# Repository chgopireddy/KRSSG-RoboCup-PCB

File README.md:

# KRSSG-RoboCup-PCB
Eagle PCB Design Files of RoboCup Hardware

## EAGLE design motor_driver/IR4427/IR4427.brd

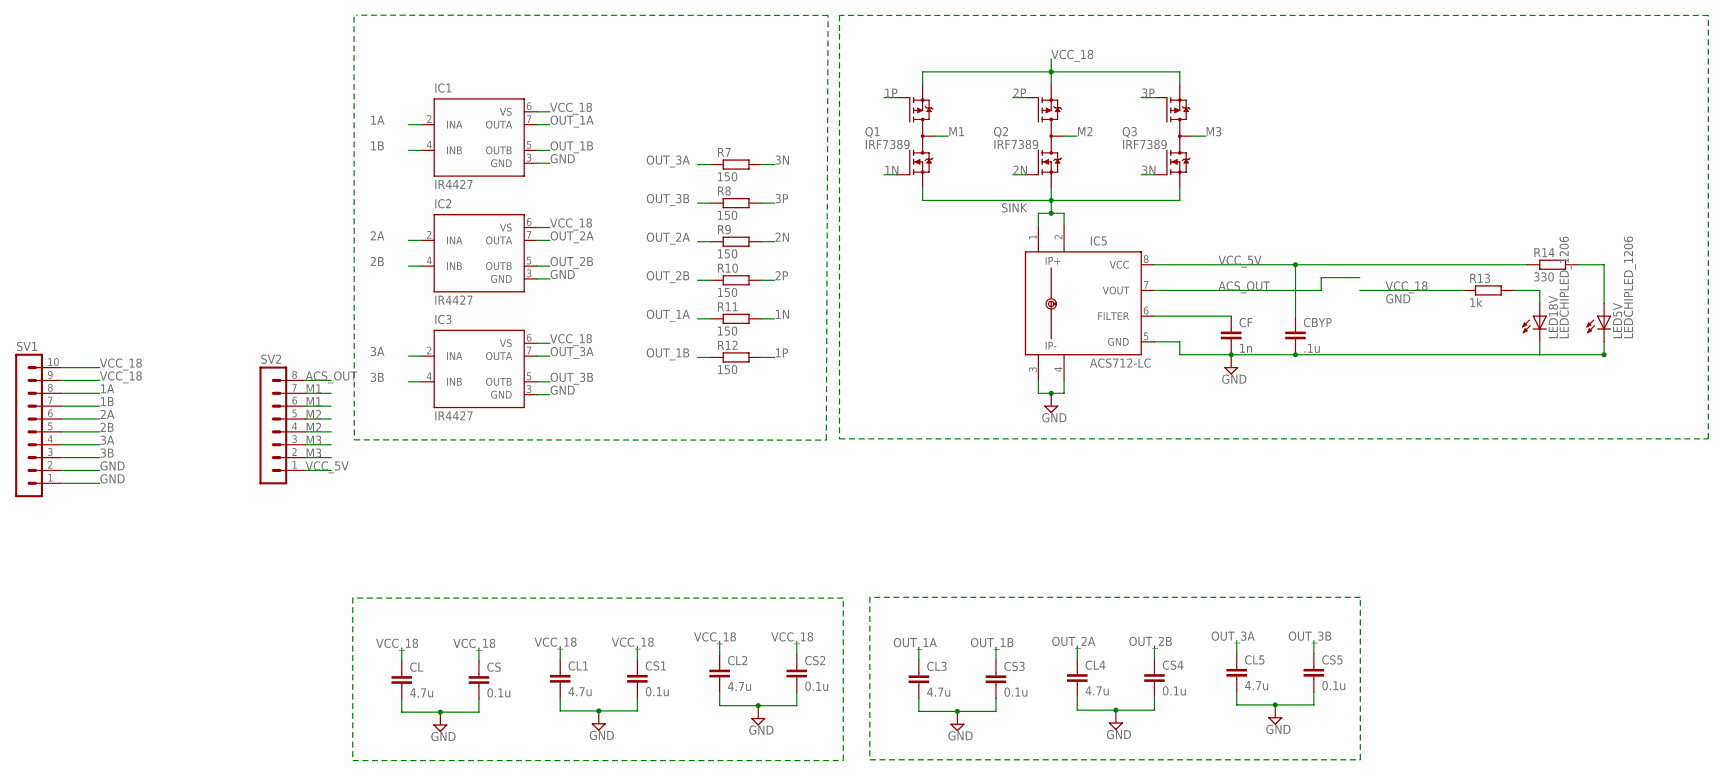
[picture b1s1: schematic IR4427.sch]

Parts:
CBYP: .1u; C1206
CF: 1n; C1206
CL, CL1, CL2, CL3, CL4, CL5: 4.7u; C1206
CS, CS1, CS2, CS3, CS4, CS5: 0.1u; C1206
IC1, IC2, IC3: IR4427; DIL08
IC5: ACS712-LC; SOIC8
LED5V, LED18V: LEDCHIPLED_1206; CHIPLED_1206
Q1, Q2, Q3: IRF7389; SO08-IRF
R7, R8, R9, R10, R11, R12: 150; R1206
R13: 1k; R1206
R14: 330; R1206
SV1: MA10-1
SV2: MA08-1

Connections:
1A: IC1.2 (INA), SV1.8
1B: IC1.4 (INB), SV1.7
1N: Q1.2 (N-G), R11.2
1P: Q1.4 (P-G), R12.2
2A: IC2.2 (INA), SV1.6
2B: IC2.4 (INB), SV1.5
2N: Q2.2 (N-G), R9.2
2P: Q2.4 (P-G), R10.2
3A: IC3.2 (INA), SV1.4
3B: IC3.4 (INB), SV1.3
3N: Q3.2 (N-G), R7.2
3P: Q3.4 (P-G), R8.2
ACS_OUT: IC5.7 (VOUT), SV2.8
GND: CBYP.2, CF.2, CL.2, CL1.2, CL2.2, CL3.2, CL4.2, CL5.2, CS.2, CS1.2, CS2.2, CS3.2, CS4.2, CS5.2, IC1.3 (GND), IC2.3 (GND), IC3.3 (GND), IC5.3 (IP-), IC5.4 (IP-1), IC5.5 (GND), LED5V.C, LED18V.C, SV1.1, SV1.2
M1: Q1.5 (D), Q1.6 (D), Q1.7 (D), Q1.8 (D), SV2.6, SV2.7
M2: Q2.5 (D), Q2.6 (D), Q2.7 (D), Q2.8 (D), SV2.4, SV2.5
M3: Q3.5 (D), Q3.6 (D), Q3.7 (D), Q3.8 (D), SV2.2, SV2.3
unnamed: LED18V.A, R13.2
unnamed: CF.1, IC5.6 (FILTER)
unnamed: LED5V.A, R14.2
OUT_1A: CL3.1, IC1.7 (OUTA), R11.1
OUT_1B: CS3.1, IC1.5 (OUTB), R12.1
OUT_2A: CL4.1, IC2.7 (OUTA), R9.1
OUT_2B: CS4.1, IC2.5 (OUTB), R10.1
OUT_3A: CL5.1, IC3.7 (OUTA), R7.1
OUT_3B: CS5.1, IC3.5 (OUTB), R8.1
SINK: IC5.1 (IP+), IC5.2 (IP+1), Q1.1 (N-S), Q2.1 (N-S), Q3.1 (N-S)
VCC_5V: CBYP.1, IC5.8 (VCC), R14.1, SV2.1
VCC_18: CL.1, CL1.1, CL2.1, CS.1, CS1.1, CS2.1, IC1.6 (VS), IC2.6 (VS), IC3.6 (VS), Q1.3 (P-S), Q2.3 (P-S), Q3.3 (P-S), R13.1, SV1.9, SV1.10

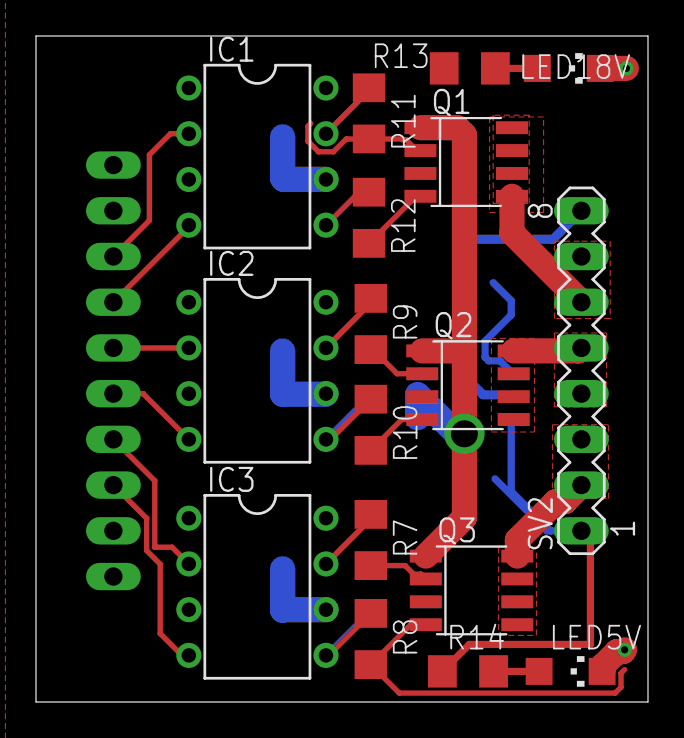
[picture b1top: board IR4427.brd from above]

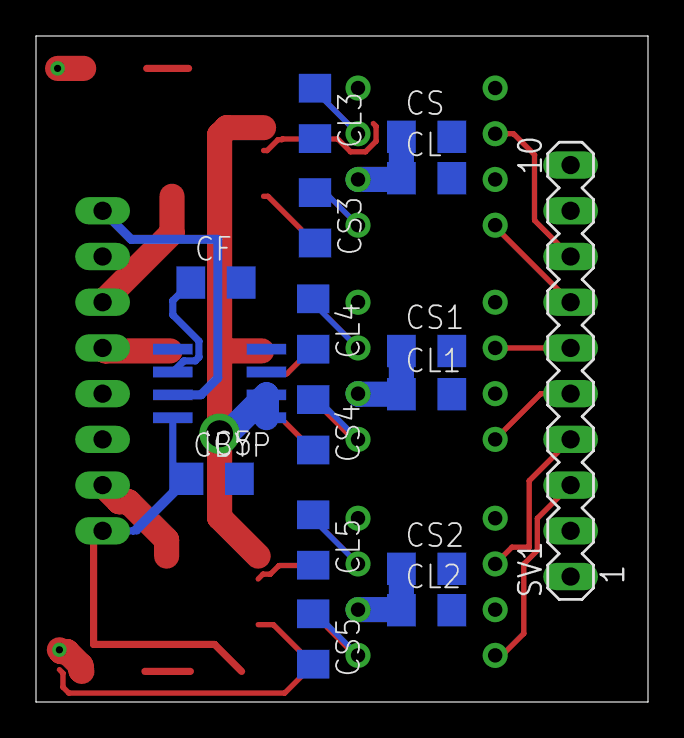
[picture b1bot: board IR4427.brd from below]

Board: 2 copper layers, 34.0 x 37.0 mm, 33 parts (16 on the bottom side), 29 nets.

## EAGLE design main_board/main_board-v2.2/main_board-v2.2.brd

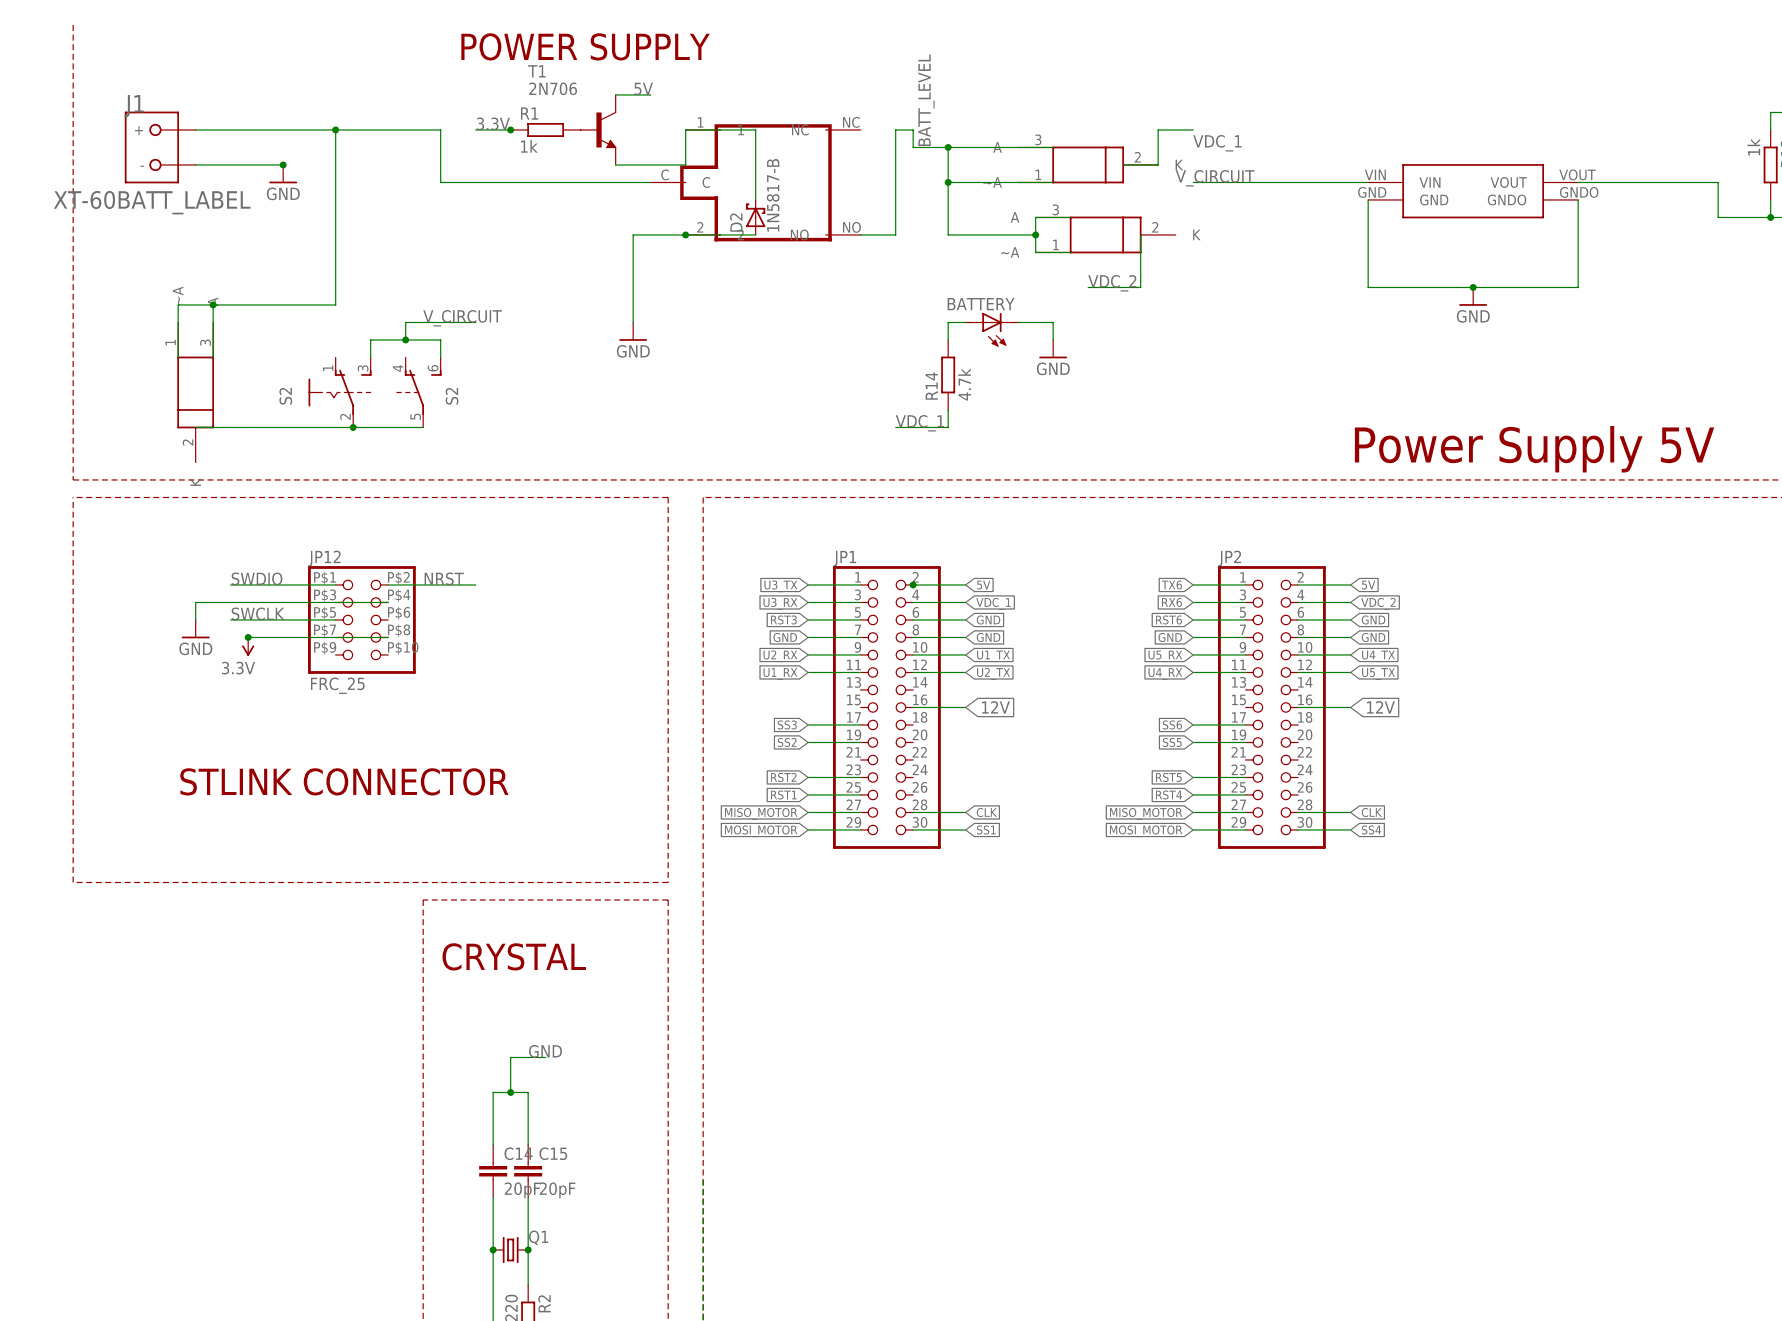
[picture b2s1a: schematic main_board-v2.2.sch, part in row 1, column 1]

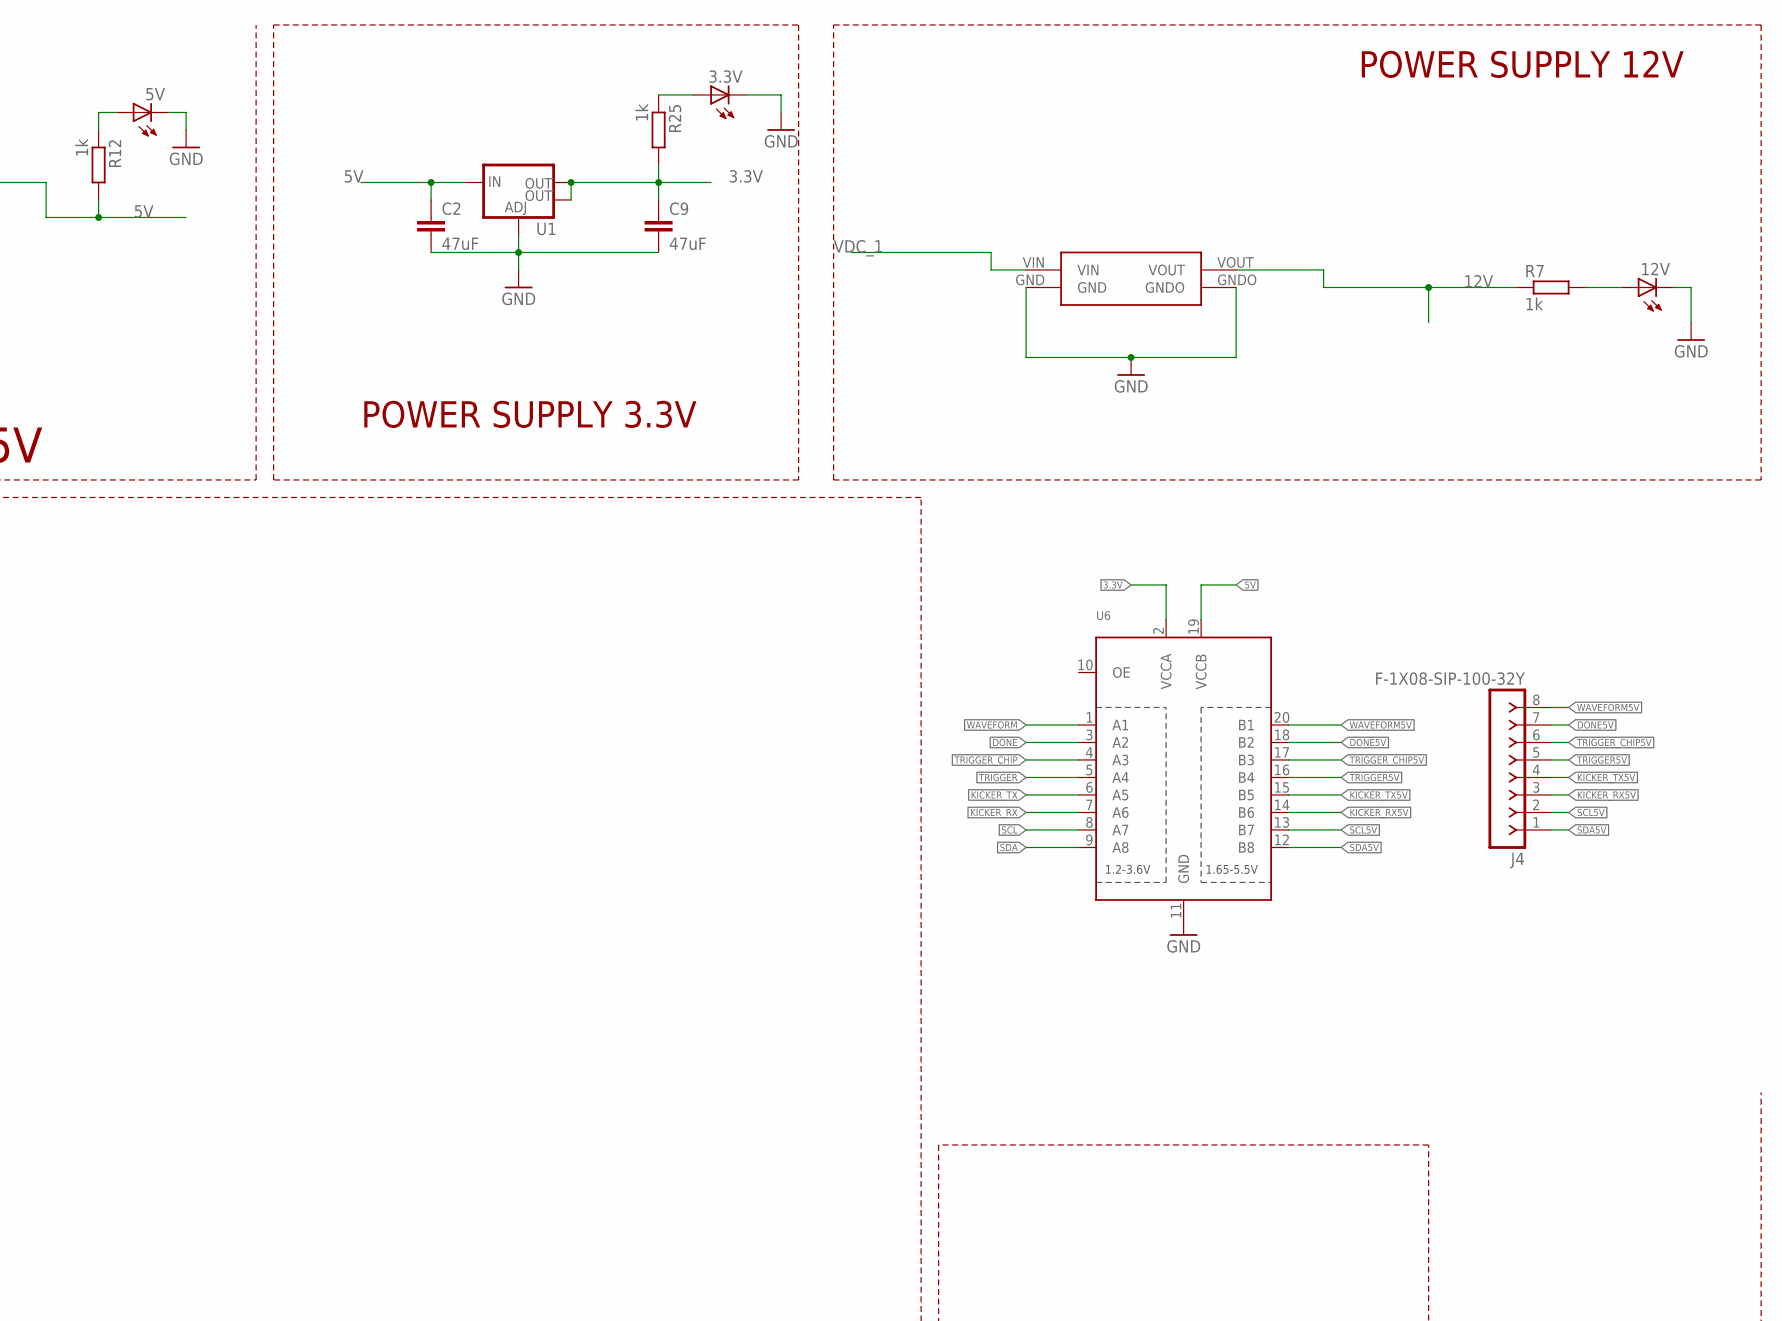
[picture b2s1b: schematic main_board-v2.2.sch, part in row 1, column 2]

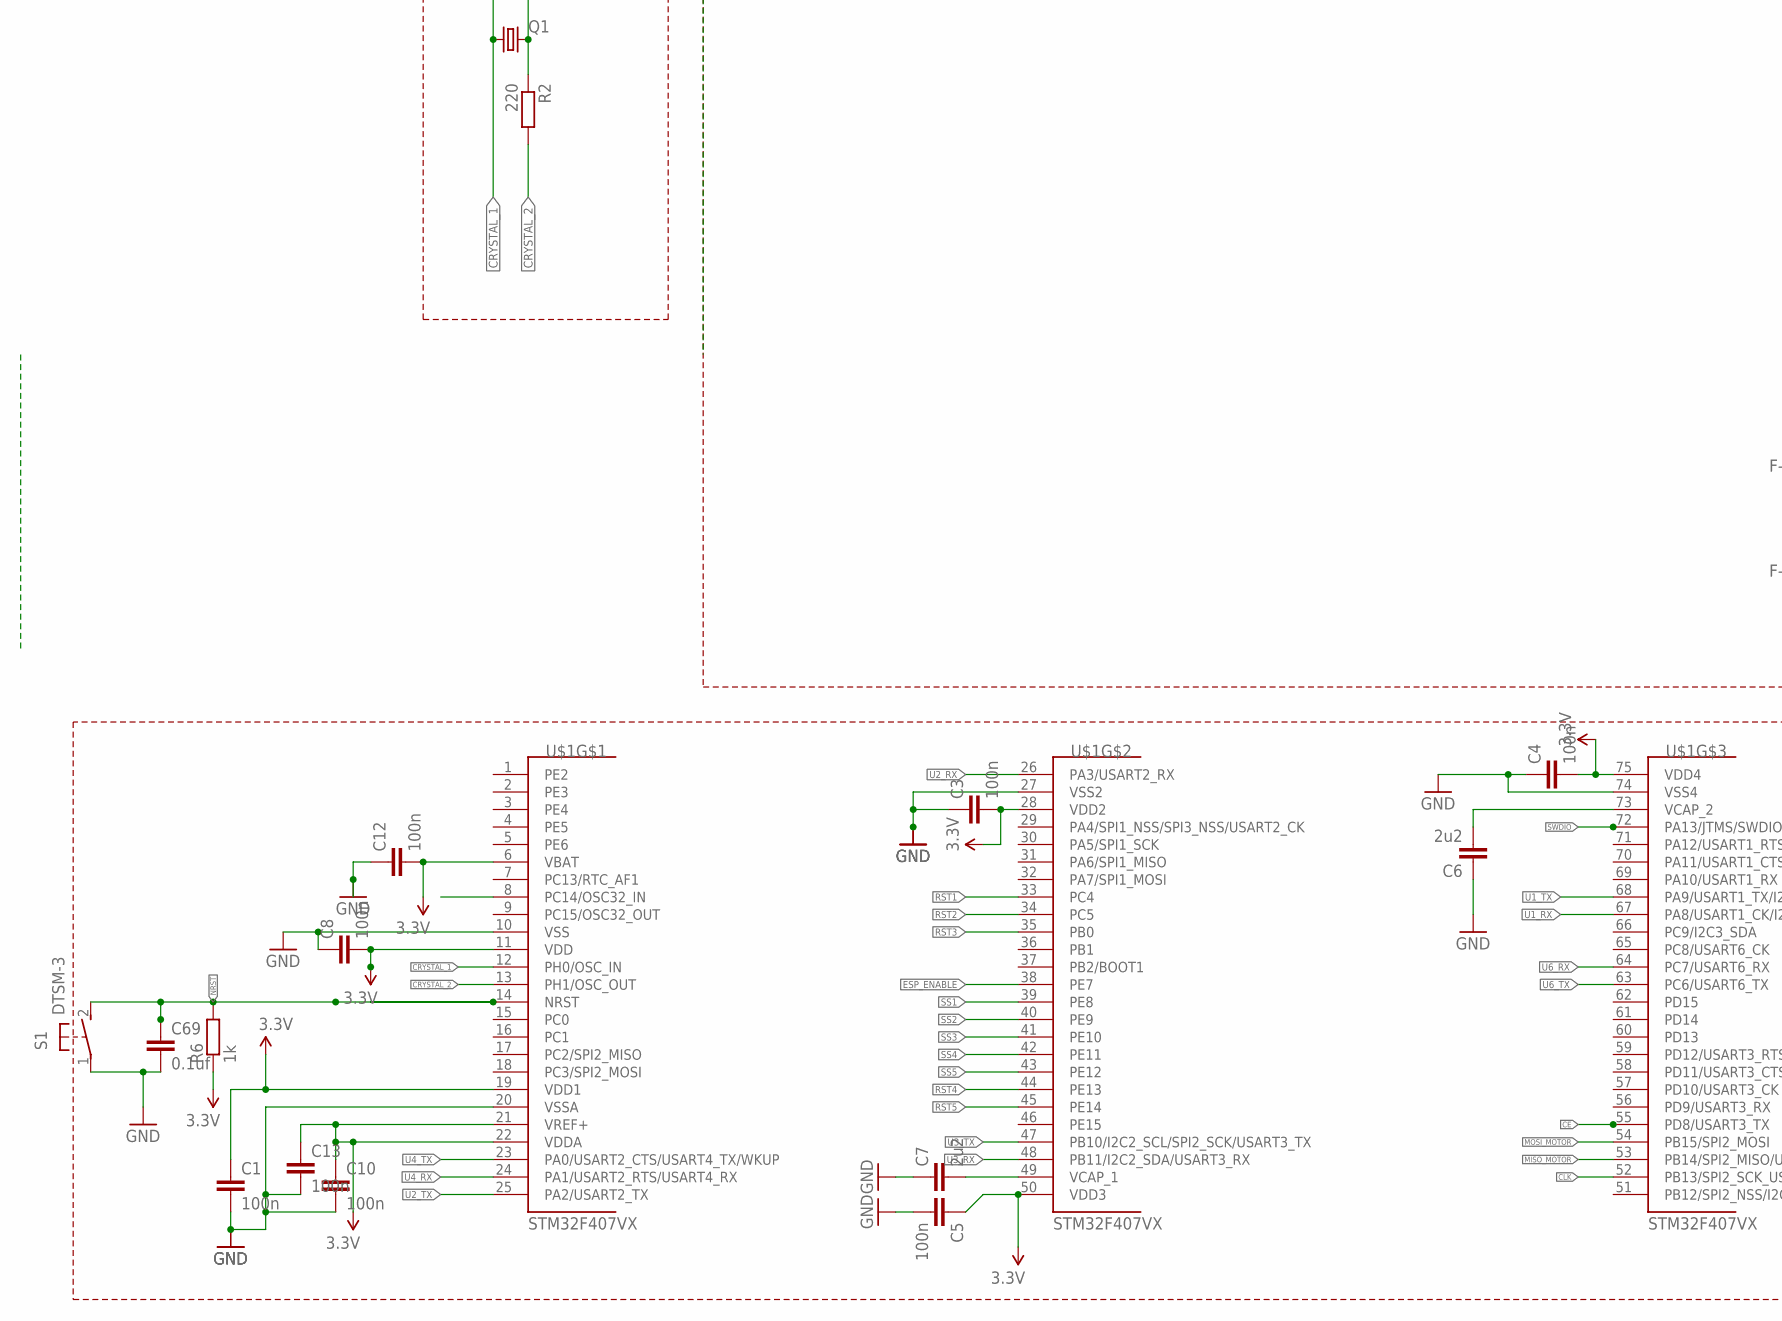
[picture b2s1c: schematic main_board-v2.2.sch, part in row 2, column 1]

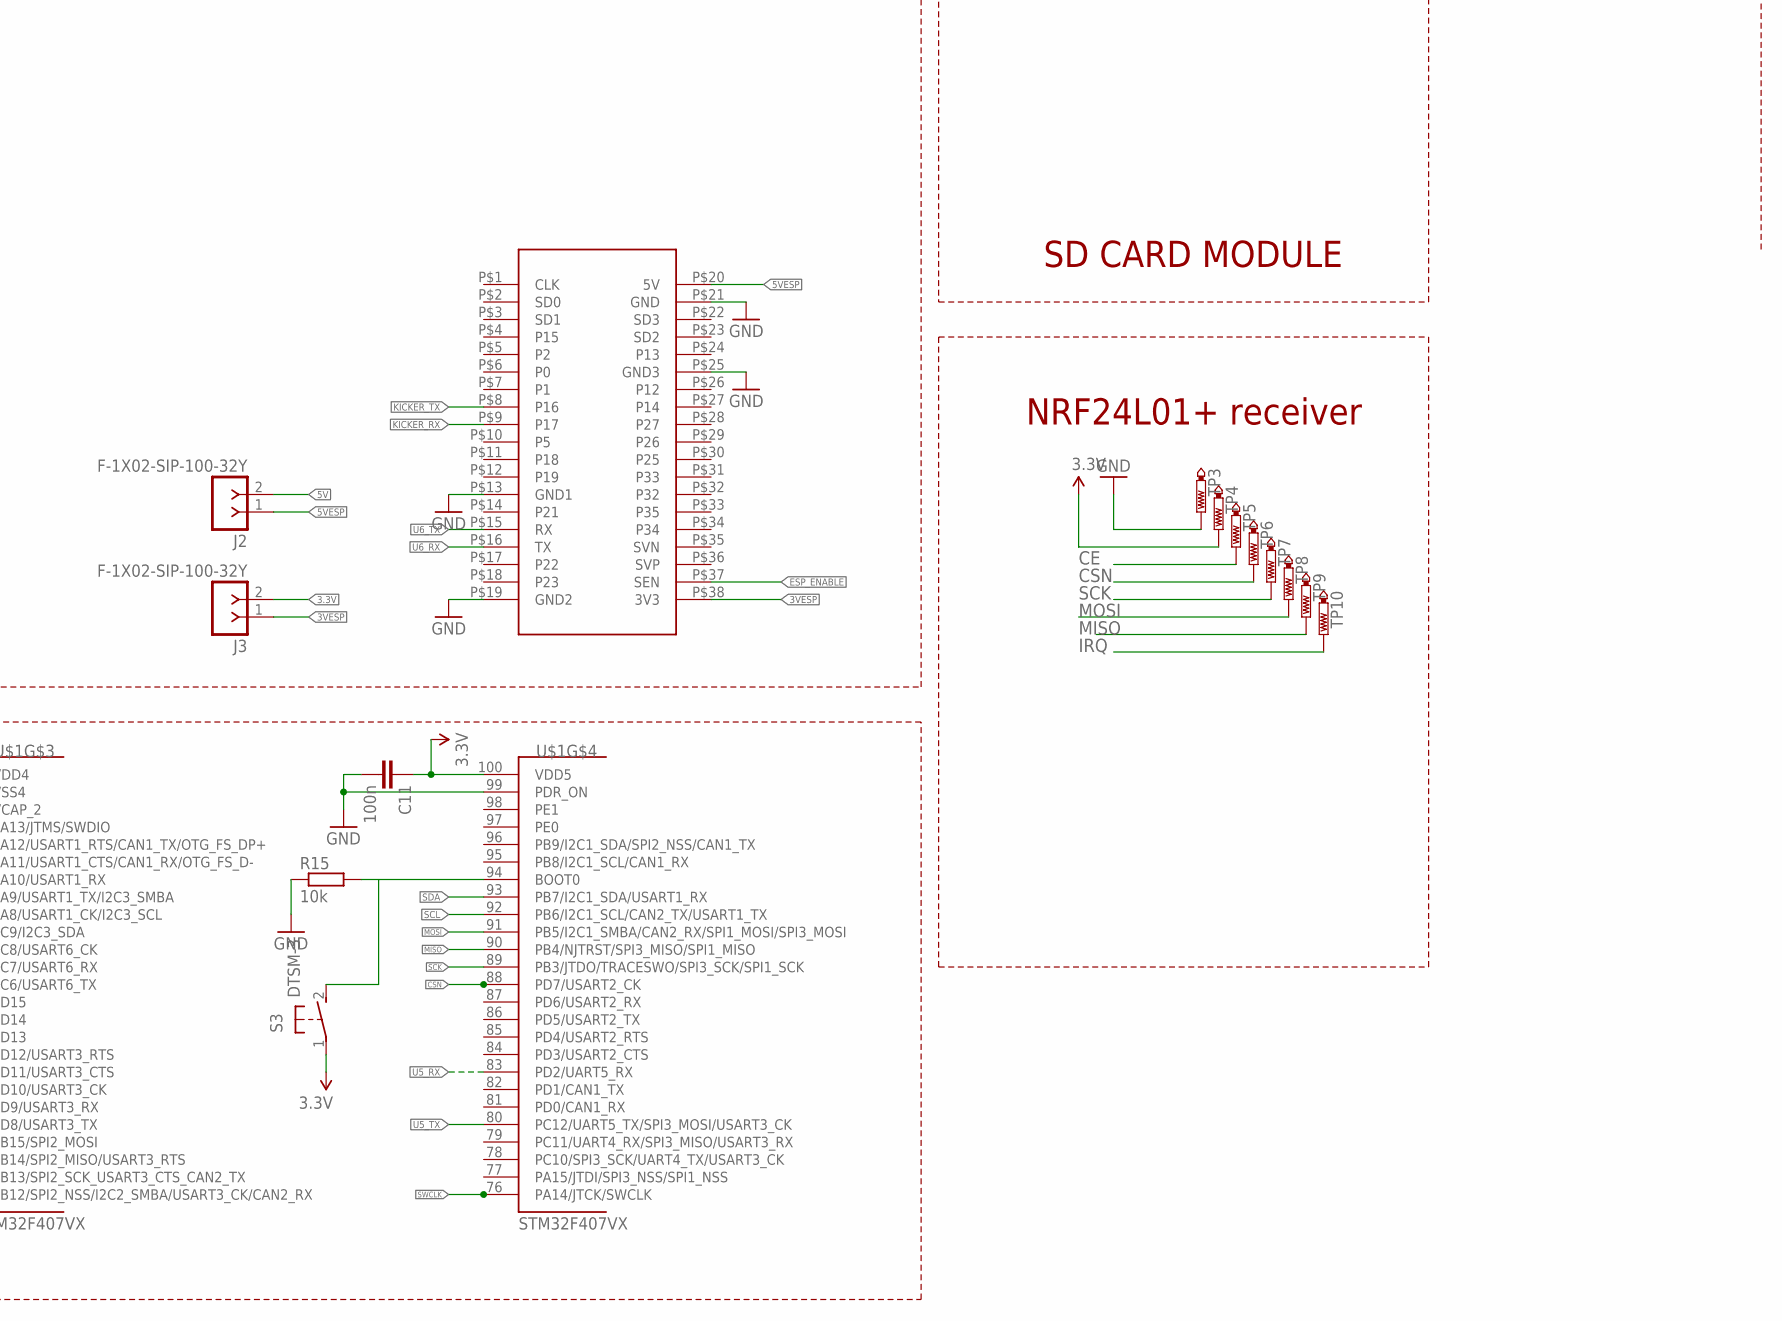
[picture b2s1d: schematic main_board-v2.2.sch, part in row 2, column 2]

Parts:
3.3V, 5V, 12V: LEDCHIPLED_0805; CHIPLED_0805
BATTERY: LEDCHIPLED_0805; CHIPLED_0805
C1, C3, C4, C5, C8, C10, C11, C12, C13: 100n; C1206
C2, C9: 47uF; C1206
C6, C7: 2u2; C1206
C14, C15: 20pF; C1206
C69: 0.1uf; C1206
D2: 1N5817-B; DO41-7.6
J1: XT-60BATT_LABEL; XT-60
J2, J3: F-1X02-SIP-100-32Y; SIP-100-02-32Y
J4: F-1X08-SIP-100-32Y; SIP-100-08-32Y
JP1, JP2: PINHD-2X15_2.54; 2X15
JP12: FRC_25; FRC2*5
Q1: CRYSTALHC49U-V; HC49U-V
R1, R6, R7, R12, R25: 1k; R1206
R2: 220; R1206
R14: 4.7k; R1206
R15: 10k; R1206
S1, S3: DTSM-3
S2: A68-A31
T1: 2N706; TO18
TP3, TP4, TP5, TP6, TP7, TP8, TP9, TP10: PTR1PAD1-13; P1-13
U1: V_REG_LM1117SOT223; SOT223
U2, U3, U4: LP38690DT-3.3; TO228P1042X238-3N
U6: TXB0108PWR; TSSOP20
U$1: STM32F407VX; LQFP100
U$2: REL
U$3, U$4: BUCK
U$6: NODEMCU32S; NODEMCU32

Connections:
3.3V: C1.1, C3.2, C4.2, C5.1, C8.2, C9.1, C10.1, C11.1, C12.2, C13.1, J3.2, JP12.P$7 (7), JP12.P$8 (8), R1.1, R6.1, R25.2, S3.1, TP4.TP, U1.2 (OUT), U1.4 (OUT), U6.2 (VCCA), U$1.6 (VBAT), U$1.11 (VDD), U$1.19 (VDD1), U$1.21 (VREF+), U$1.22 (VDDA), U$1.28 (VDD2), U$1.50 (VDD3), U$1.75 (VDD4), U$1.100 (VDD5)
3VESP: J3.1, U$6.P$38 (3V3)
5V: C2.1, J2.2, JP1.2, JP2.2, R12.2, T1.3 (C), U1.3 (IN), U6.19 (VCCB), U$3.VOUT
5VESP: J2.1, U$6.P$20 (5V)
12V: JP1.16, JP2.16, R7.1, U$4.VOUT
BATT_LEVEL: U2.1 (~A), U2.3 (A), U4.1 (~A), U4.3 (A), U$2.NO
CE: TP5.TP, U$1.55 (PD8/USART3_TX)
CLK: JP1.28, JP2.28, U$1.52 (PB13/SPI2_SCK_USART3_CTS_CAN2_TX)
CRYSTAL_1: C14.2, Q1.1, U$1.12 (PH0/OSC_IN)
CRYSTAL_2: R2.2, U$1.13 (PH1/OSC_OUT)
CSN: TP6.TP, U$1.88 (PD7/USART2_CK)
DONE: U6.3 (A2)
DONE5V: J4.7, U6.18 (B2)
ESP_ENABLE: U$1.38 (PE7), U$6.P$37 (SEN)
GND: 3.3V.C, 5V.C, 12V.C, BATTERY.C, C1.2, C2.2, C3.1, C4.1, C5.2, C6.1, C7.1, C8.1, C9.2, C10.2, C11.2, C12.1, C13.2, C14.1, C15.1, C69.2, D2.A, J1.GND (-), JP1.6, JP1.7, JP1.8, JP2.6, JP2.7, JP2.8, JP12.P$3 (3), JP12.P$4 (4), R15.1, S1.1, TP3.TP, U1.1 (ADJ), U6.11 (GND), U$1.10 (VSS), U$1.20 (VSSA), U$1.27 (VSS2), U$1.74 (VSS4), U$1.99 (PDR_ON), U$2.2, U$3.GND, U$3.GNDO, U$4.GND, U$4.GNDO, U$6.P$13 (GND1), U$6.P$19 (GND2), U$6.P$21 (GND), U$6.P$25 (GND3)
INPUT: J1.BATT (+), U3.1 (~A), U3.3 (A), U$2.C
IRQ: TP10.TP
IRQ_SPI2: U$1.8 (PC14/OSC32_IN)
KICKER_RX: U6.7 (A6), U$6.P$9 (P17)
KICKER_RX5V: J4.3, U6.14 (B6)
KICKER_TX: U6.6 (A5), U$6.P$8 (P16)
KICKER_TX5V: J4.4, U6.15 (B5)
MISO: TP9.TP, U$1.90 (PB4/NJTRST/SPI3_MISO/SPI1_MISO)
MISO_MOTOR: JP1.27, JP2.27, U$1.53 (PB14/SPI2_MISO/USART3_RTS)
MOSI: TP8.TP, U$1.91 (PB5/I2C1_SMBA/CAN2_RX/SPI1_MOSI/SPI3_MO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)
MOSI_MOTOR: JP1.29, JP2.29, U$1.54 (PB15/SPI2_MOSI)
unnamed: C7.2, U$1.49 (VCAP_1)
unnamed: C6.2, U$1.73 (VCAP_2)
unnamed: R15.2, S3.2, U$1.94 (BOOT0)
unnamed: C15.2, Q1.2, R2.1
unnamed: 5V.A, R12.1
unnamed: 12V.A, R7.2
unnamed: BATTERY.A, R14.2
unnamed: 3.3V.A, R25.1
unnamed: R1.2, T1.2 (B)
unnamed: D2.C, T1.1 (E), U$2.1
unnamed: S2.2, S2.5, U3.2 (K)
NRST: C69.1, JP12.P$2 (2), R6.2, S1.2, U$1.14 (NRST)
RST1: JP1.25, U$1.33 (PC4)
RST2: JP1.23, U$1.34 (PC5)
RST3: JP1.5, U$1.35 (PB0)
RST4: JP2.25, U$1.44 (PE13)
RST5: JP2.23, U$1.45 (PE14)
RST6: JP2.5
RX6: JP2.3
SCK: TP7.TP, U$1.89 (PB3/JTDO/TRACESWO/SPI3_SCK/SPI1_SCK)
SCL: U6.8 (A7), U$1.92 (PB6/I2C1_SCL/CAN2_TX/USART1_TX)
SCL5V: J4.2, U6.13 (B7)
SDA: U6.9 (A8), U$1.93 (PB7/I2C1_SDA/USART1_RX)
SDA5V: J4.1, U6.12 (B8)
SS1: JP1.30, U$1.39 (PE8)
SS2: JP1.19, U$1.40 (PE9)
SS3: JP1.17, U$1.41 (PE10)
SS4: JP2.30, U$1.42 (PE11)
SS5: JP2.19, U$1.43 (PE12)
SS6: JP2.17
SWCLK: JP12.P$5 (5), U$1.76 (PA14/JTCK/SWCLK)
SWDIO: JP12.P$1 (1), U$1.72 (PA13/JTMS/SWDIO)
TRIGGER: U6.5 (A4)
TRIGGER5V: J4.5, U6.16 (B4)
TRIGGER_CHIP: U6.4 (A3)
TRIGGER_CHIP5V: J4.6, U6.17 (B3)
TX6: JP2.1
U1_RX: JP1.11, U$1.67 (PA8/USART1_CK/I2C3_SCL)
U1_TX: JP1.10, U$1.68 (PA9/USART1_TX/I2C3_SMBA)
U2_RX: JP1.9, U$1.26 (PA3/USART2_RX)
U2_TX: JP1.12, U$1.25 (PA2/USART2_TX)
U3_RX: JP1.3, U$1.48 (PB11/I2C2_SDA/USART3_RX)
U3_TX: JP1.1, U$1.47 (PB10/I2C2_SCL/SPI2_SCK/USART3_TX)
U4_RX: JP2.11, U$1.24 (PA1/USART2_RTS/USART4_RX)
U4_TX: JP2.10, U$1.23 (PA0/USART2_CTS/USART4_TX/WKUP)
U5_RX: JP2.9, U$1.83 (PD2/UART5_RX)
U5_TX: JP2.12, U$1.80 (PC12/UART5_TX/SPI3_MOSI/USART3_CK)
U6_RX: U$1.64 (PC7/USART6_RX), U$6.P$16 (TX)
U6_TX: U$1.63 (PC6/USART6_TX), U$6.P$15 (RX)
VDC_1: JP1.4, R14.1, U4.2 (K), U$4.VIN
VDC_2: JP2.4, U2.2 (K)
V_CIRCUIT: S2.3 (S), S2.6 (S), U$3.VIN
WAVEFORM: U6.1 (A1)
WAVEFORM5V: J4.8, U6.20 (B1)

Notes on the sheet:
NRF24L01+ receiver
STLINK CONNECTOR
POWER SUPPLY 12V
POWER SUPPLY 3.3V
POWER SUPPLY
Power Supply 5V
CRYSTAL
SD CARD MODULE

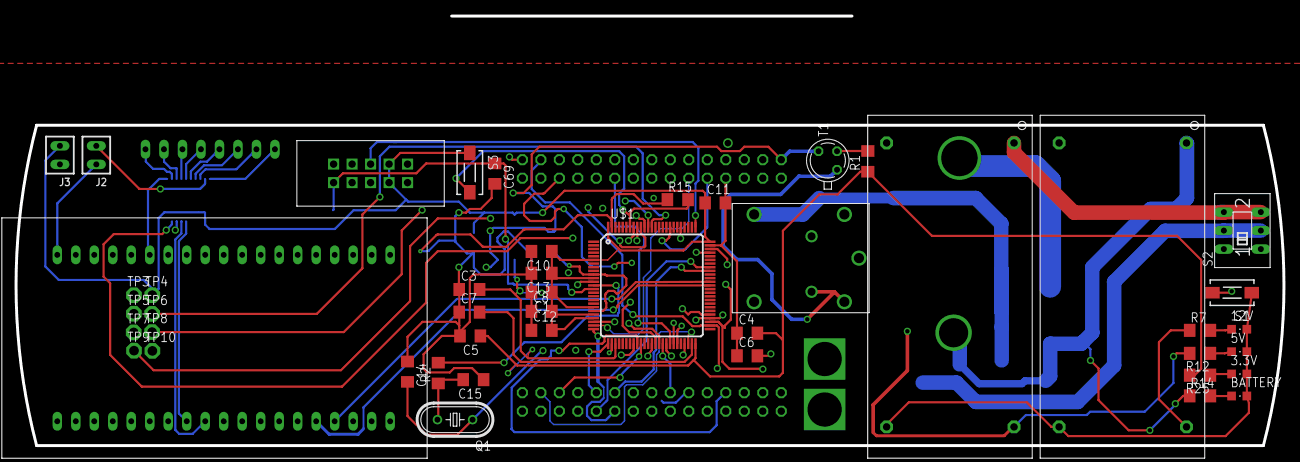
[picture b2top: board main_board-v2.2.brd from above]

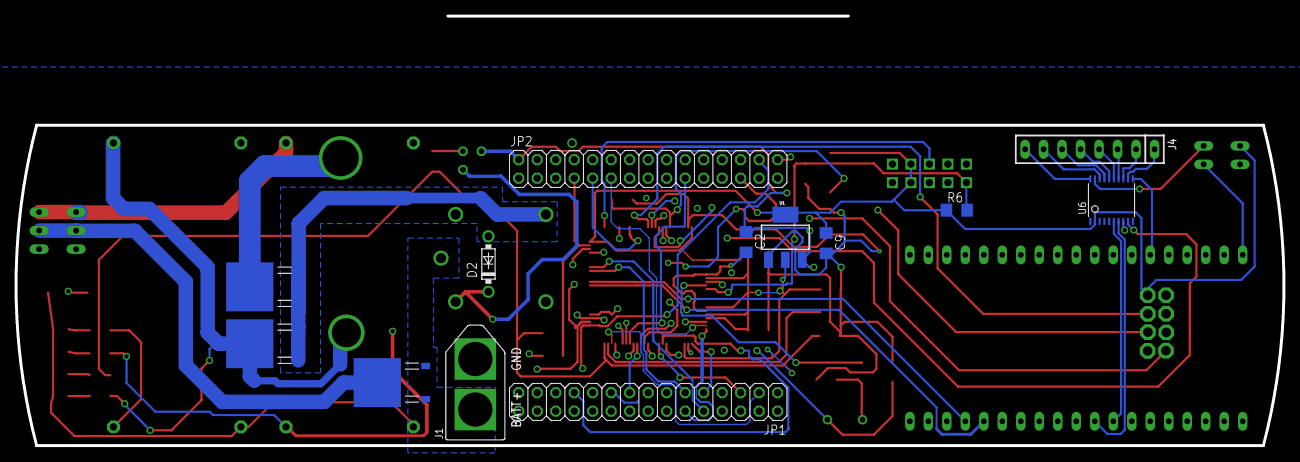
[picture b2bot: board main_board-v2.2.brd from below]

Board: 4 copper layers, 174.2 x 44.0 mm, 59 parts (13 on the bottom side), 70 nets.

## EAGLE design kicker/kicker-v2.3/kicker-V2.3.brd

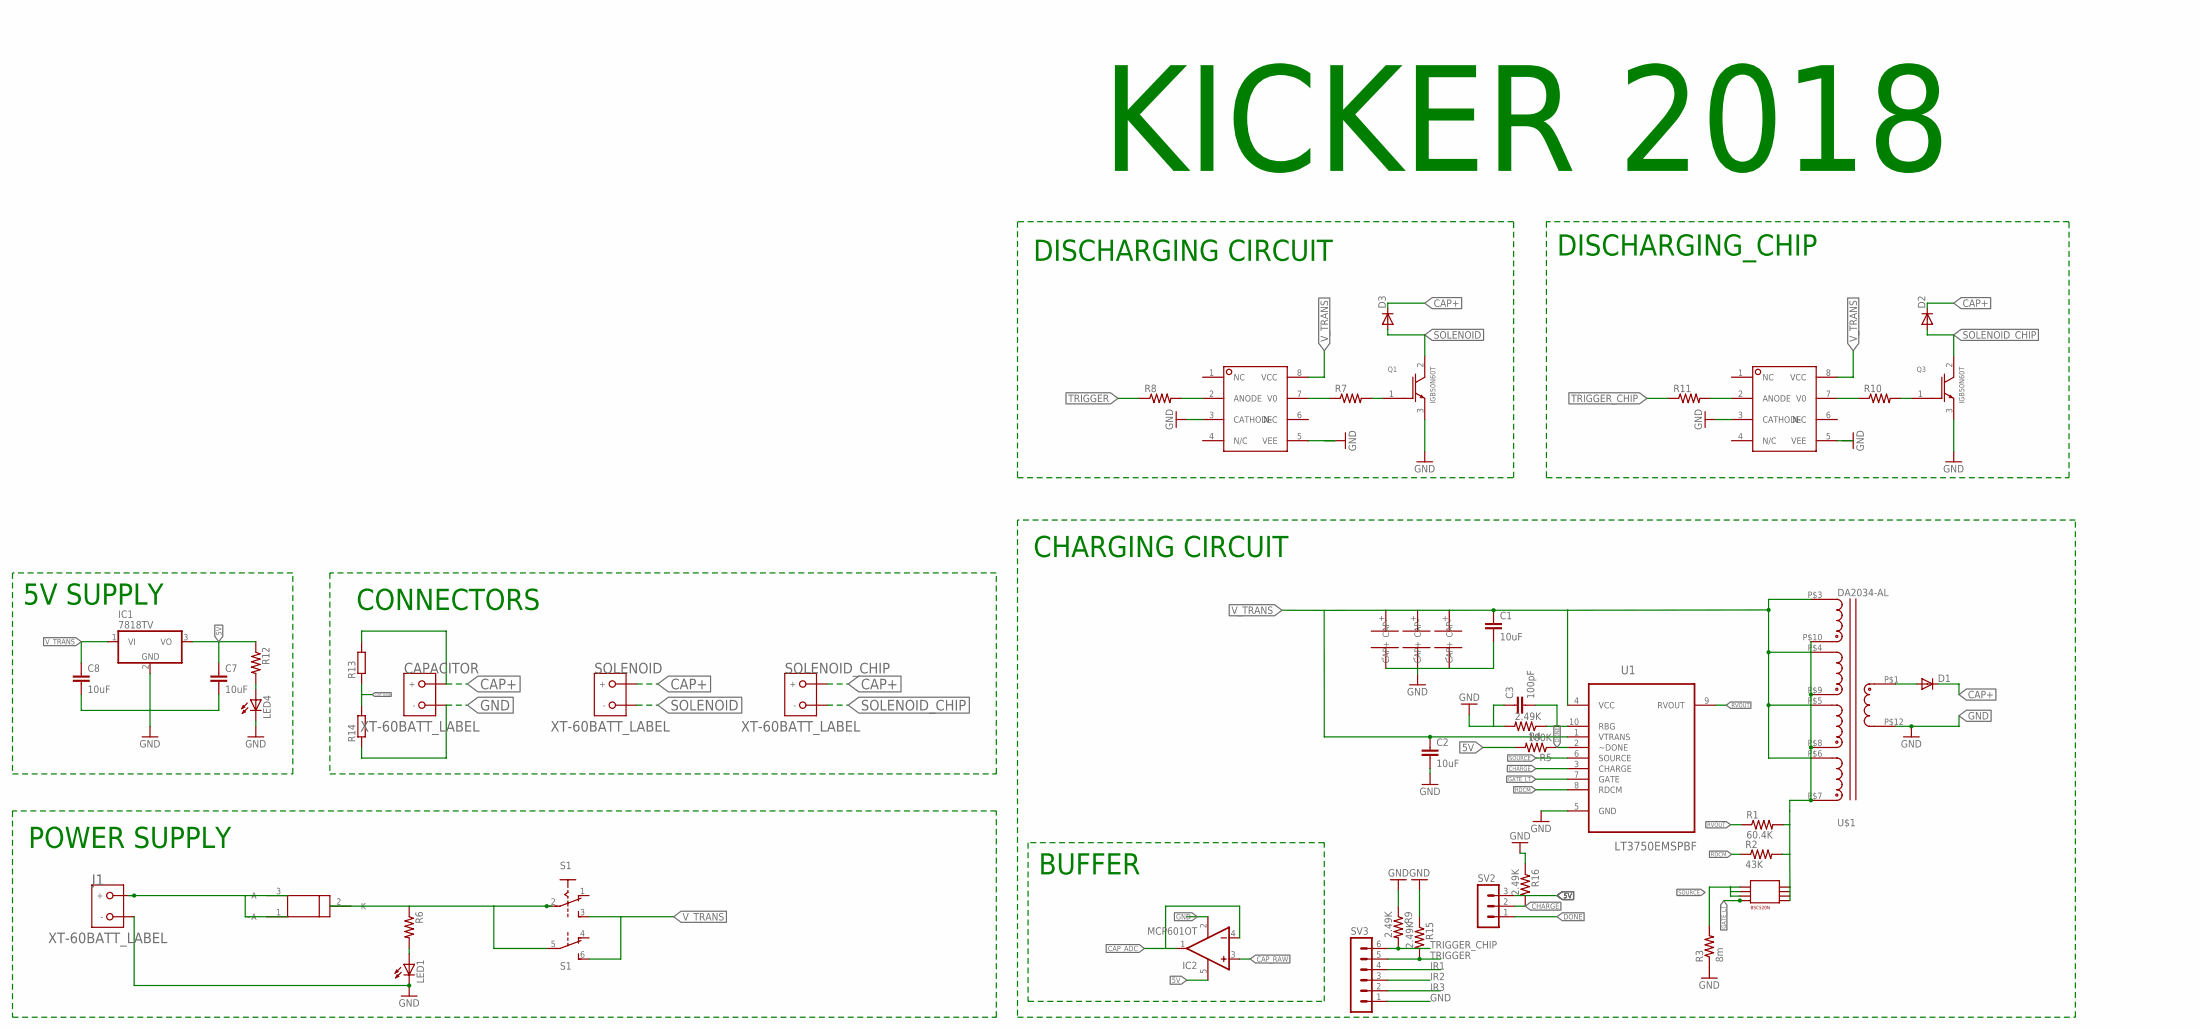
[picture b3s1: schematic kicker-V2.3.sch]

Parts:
C1, C2, C7, C8: 10uF; C1206
C3: 100pF; C1206
CAPACITOR: XT-60BATT_LABEL; XT-60
D1, D2, D3: DIODE-DO214AA; DO214AA
IC1: 7818TV; TO220V
IC2: MCP601OT; SOT23-5
J1: XT-60BATT_LABEL; XT-60
LED1, LED4: LEDCHIPLED_1206; CHIPLED_1206
Q1, Q3: IGB50N60T; TO254P1524X457-3N-2-V
R1: 60.4K; M1206
R2: 43K; M1206
R3: 8m; M1206
R4, R9, R15, R16: 2.49K; M1206
R5: 100K; M1206
R6, R7, R8, R10, R11, R12: R-US_M1206; M1206
R13, R14: R-EU_R0805; R0805
S1: A68-A31
SOLENOID: XT-60BATT_LABEL; XT-60
SOLENOID_CHIP: XT-60BATT_LABEL; XT-60
SV2: MA03-1
SV3: MA06-1
U1: LT3750EMSPBF; SOP50P490X110-10N
U3: LP38690DT-3.3; TO228P1042X238-3N
U$1: DA2034-AL
U$2, U$3, U$4: 56uF; SVP_F12
U$5: BSC520N; PG-TDSON-8
U$6, U$7: HCPL-3120-300E; DIL08

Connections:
5V: C7.1, IC1.3 (VO), IC2.5 (V+), R5.2, R12.1, SV2.3
CAP+: CAPACITOR.BATT (+), D1.C, D2.C, D3.C, R13.2, SOLENOID.BATT (+), SOLENOID_CHIP.BATT (+)
CAP_ADC: IC2.1 (OUT), IC2.4 (-IN)
CAP_RAW: IC2.3 (+IN), R13.1, R14.2
CHARGE: R16.2, SV2.2, U1.3 (CHARGE)
DONE: R5.1, SV2.1, U1.2 (~DONE)
GATE_LT: U1.7 (GATE), U$5.G
GND: C1.2, C2.2, C3.1, C7.2, C8.2, CAPACITOR.GND (-), IC1.2 (GND), IC2.2 (V-), J1.GND (-), LED1.C, LED4.C, Q1.3 (EMITTER), Q3.3 (EMITTER), R3.1, R4.2, R9.1, R14.1, R15.1, R16.1, SV3.1, U1.5 (GND), U$1.P$12 (12), U$2.- (CAP-), U$3.- (CAP-), U$4.- (CAP-), U$6.3 (CATHODE), U$6.5 (VEE), U$7.3 (CATHODE), U$7.5 (VEE)
IR1: SV3.4
IR2: SV3.3
IR3: SV3.2
unnamed: R7.1, U$6.7 (V0)
unnamed: C3.2, R4.1, U1.10 (RBG)
unnamed: R6.1, S1.2, S1.5, U3.2 (K)
unnamed: Q1.1 (GATE), R7.2
unnamed: R8.2, U$6.2 (ANODE)
unnamed: D1.A, U$1.P$1 (1)
unnamed: LED1.A, R6.2
unnamed: R10.1, U$7.7 (V0)
unnamed: Q3.1 (GATE), R10.2
unnamed: R11.2, U$7.2 (ANODE)
unnamed: LED4.A, R12.2
RDCM: R2.1, U1.8 (RDCM)
RVOUT: R1.1, U1.9 (RVOUT)
SINK: R1.2, R2.2, U$1.P$7 (7), U$1.P$8 (8), U$1.P$9 (9), U$1.P$10 (10), U$5.D1, U$5.D2, U$5.D3, U$5.D4
SOLENOID: D3.A, Q1.2 (COLLECTOR), SOLENOID.GND (-)
SOLENOID_CHIP: D2.A, Q3.2 (COLLECTOR), SOLENOID_CHIP.GND (-)
SOURCE: R3.2, U1.6 (SOURCE), U$5.S1, U$5.S2, U$5.S3
TRIGGER: R8.1, R15.2, SV3.5
TRIGGER_CHIP: R9.2, R11.1, SV3.6
VIN: J1.BATT (+), U3.1 (~A), U3.3 (A)
V_TRANS: C1.1, C2.1, C8.1, IC1.1 (VI), S1.3 (S), S1.6 (S), U1.1 (VTRANS), U1.4 (VCC), U$1.P$3 (3), U$1.P$4 (4), U$1.P$5 (5), U$1.P$6 (6), U$2.+ (CAP+), U$3.+ (CAP+), U$4.+ (CAP+), U$6.8 (VCC), U$7.8 (VCC)

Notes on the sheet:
DISCHARGING CIRCUIT
POWER SUPPLY
CHARGING CIRCUIT
DISCHARGING_CHIP
5V SUPPLY
CONNECTORS
KICKER 2018
BUFFER

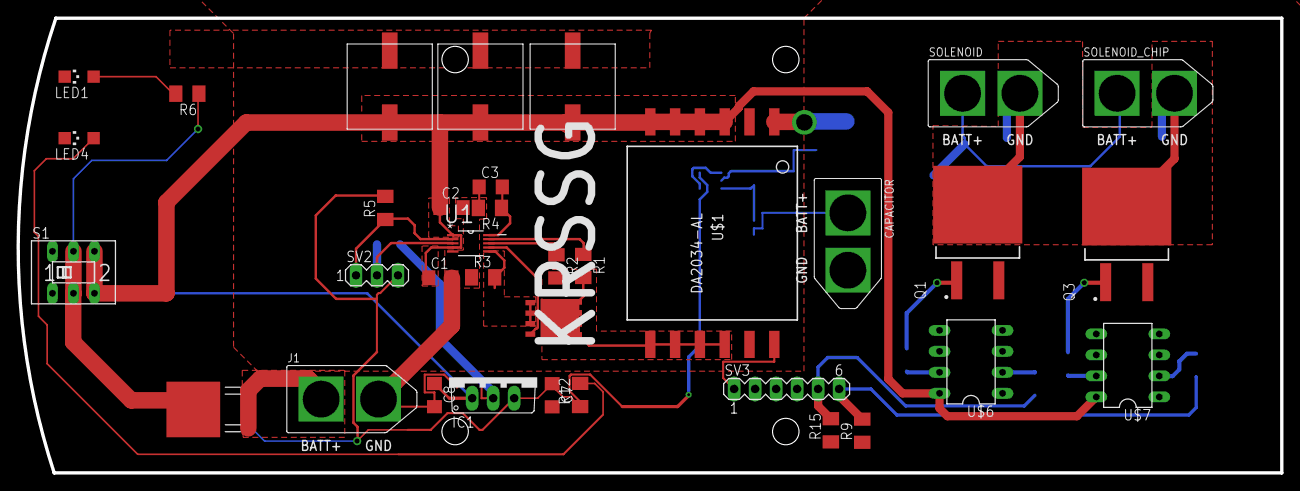
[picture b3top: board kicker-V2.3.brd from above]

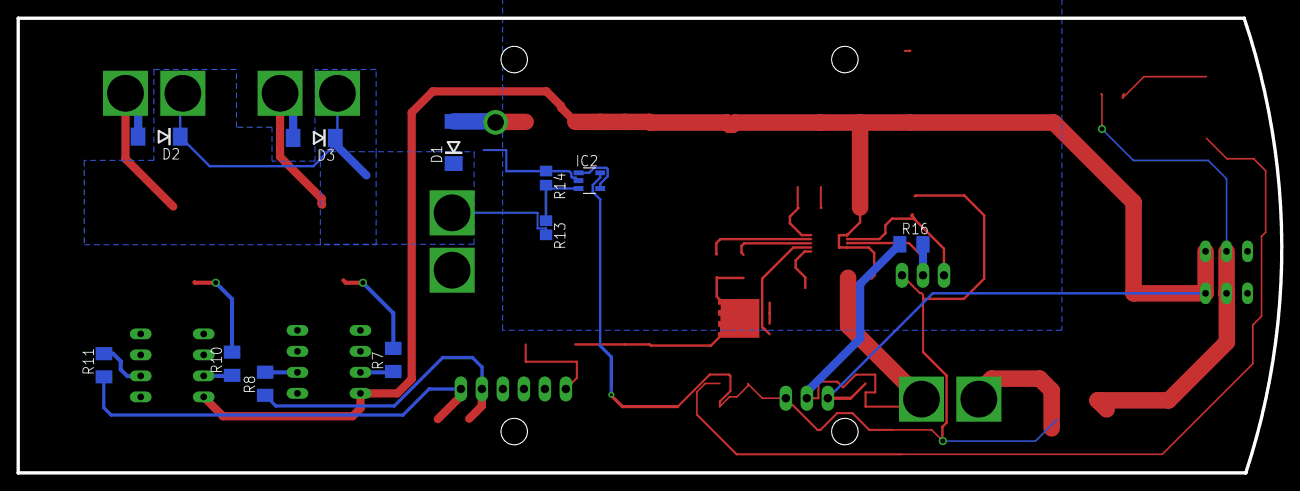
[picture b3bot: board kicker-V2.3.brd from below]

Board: 2 copper layers, 152.9 x 55.0 mm, 46 parts (11 on the bottom side), 29 nets.

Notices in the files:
parts and their libraries:
SparkFun-PowerIC: Licensing: Creative Commons ShareAlike 4.0 International - https://creativecommons.org/licenses/by-sa/4.0
con-headers-jp: Copyright (C) 2008, Bob Starr
STM32F407Vx_LQFP100: Copyright 2012 by Ersan Günes, Quantitec, info@quantitec.de
